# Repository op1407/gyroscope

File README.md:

# gyroscope

A simple Gyroscope using RP2040 based PCB, MPU-6050 and ST7735 1,8" TFT Display

3D model was created using DesignSpark Mechanical 5.0

PCB was created using KiCad 6.0

License: CC BY 4.0
https://creativecommons.org/licenses/by/4.0/

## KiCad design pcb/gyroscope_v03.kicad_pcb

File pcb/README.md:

# KiCad files

PCB design files

Some symbols and footprints are also missing

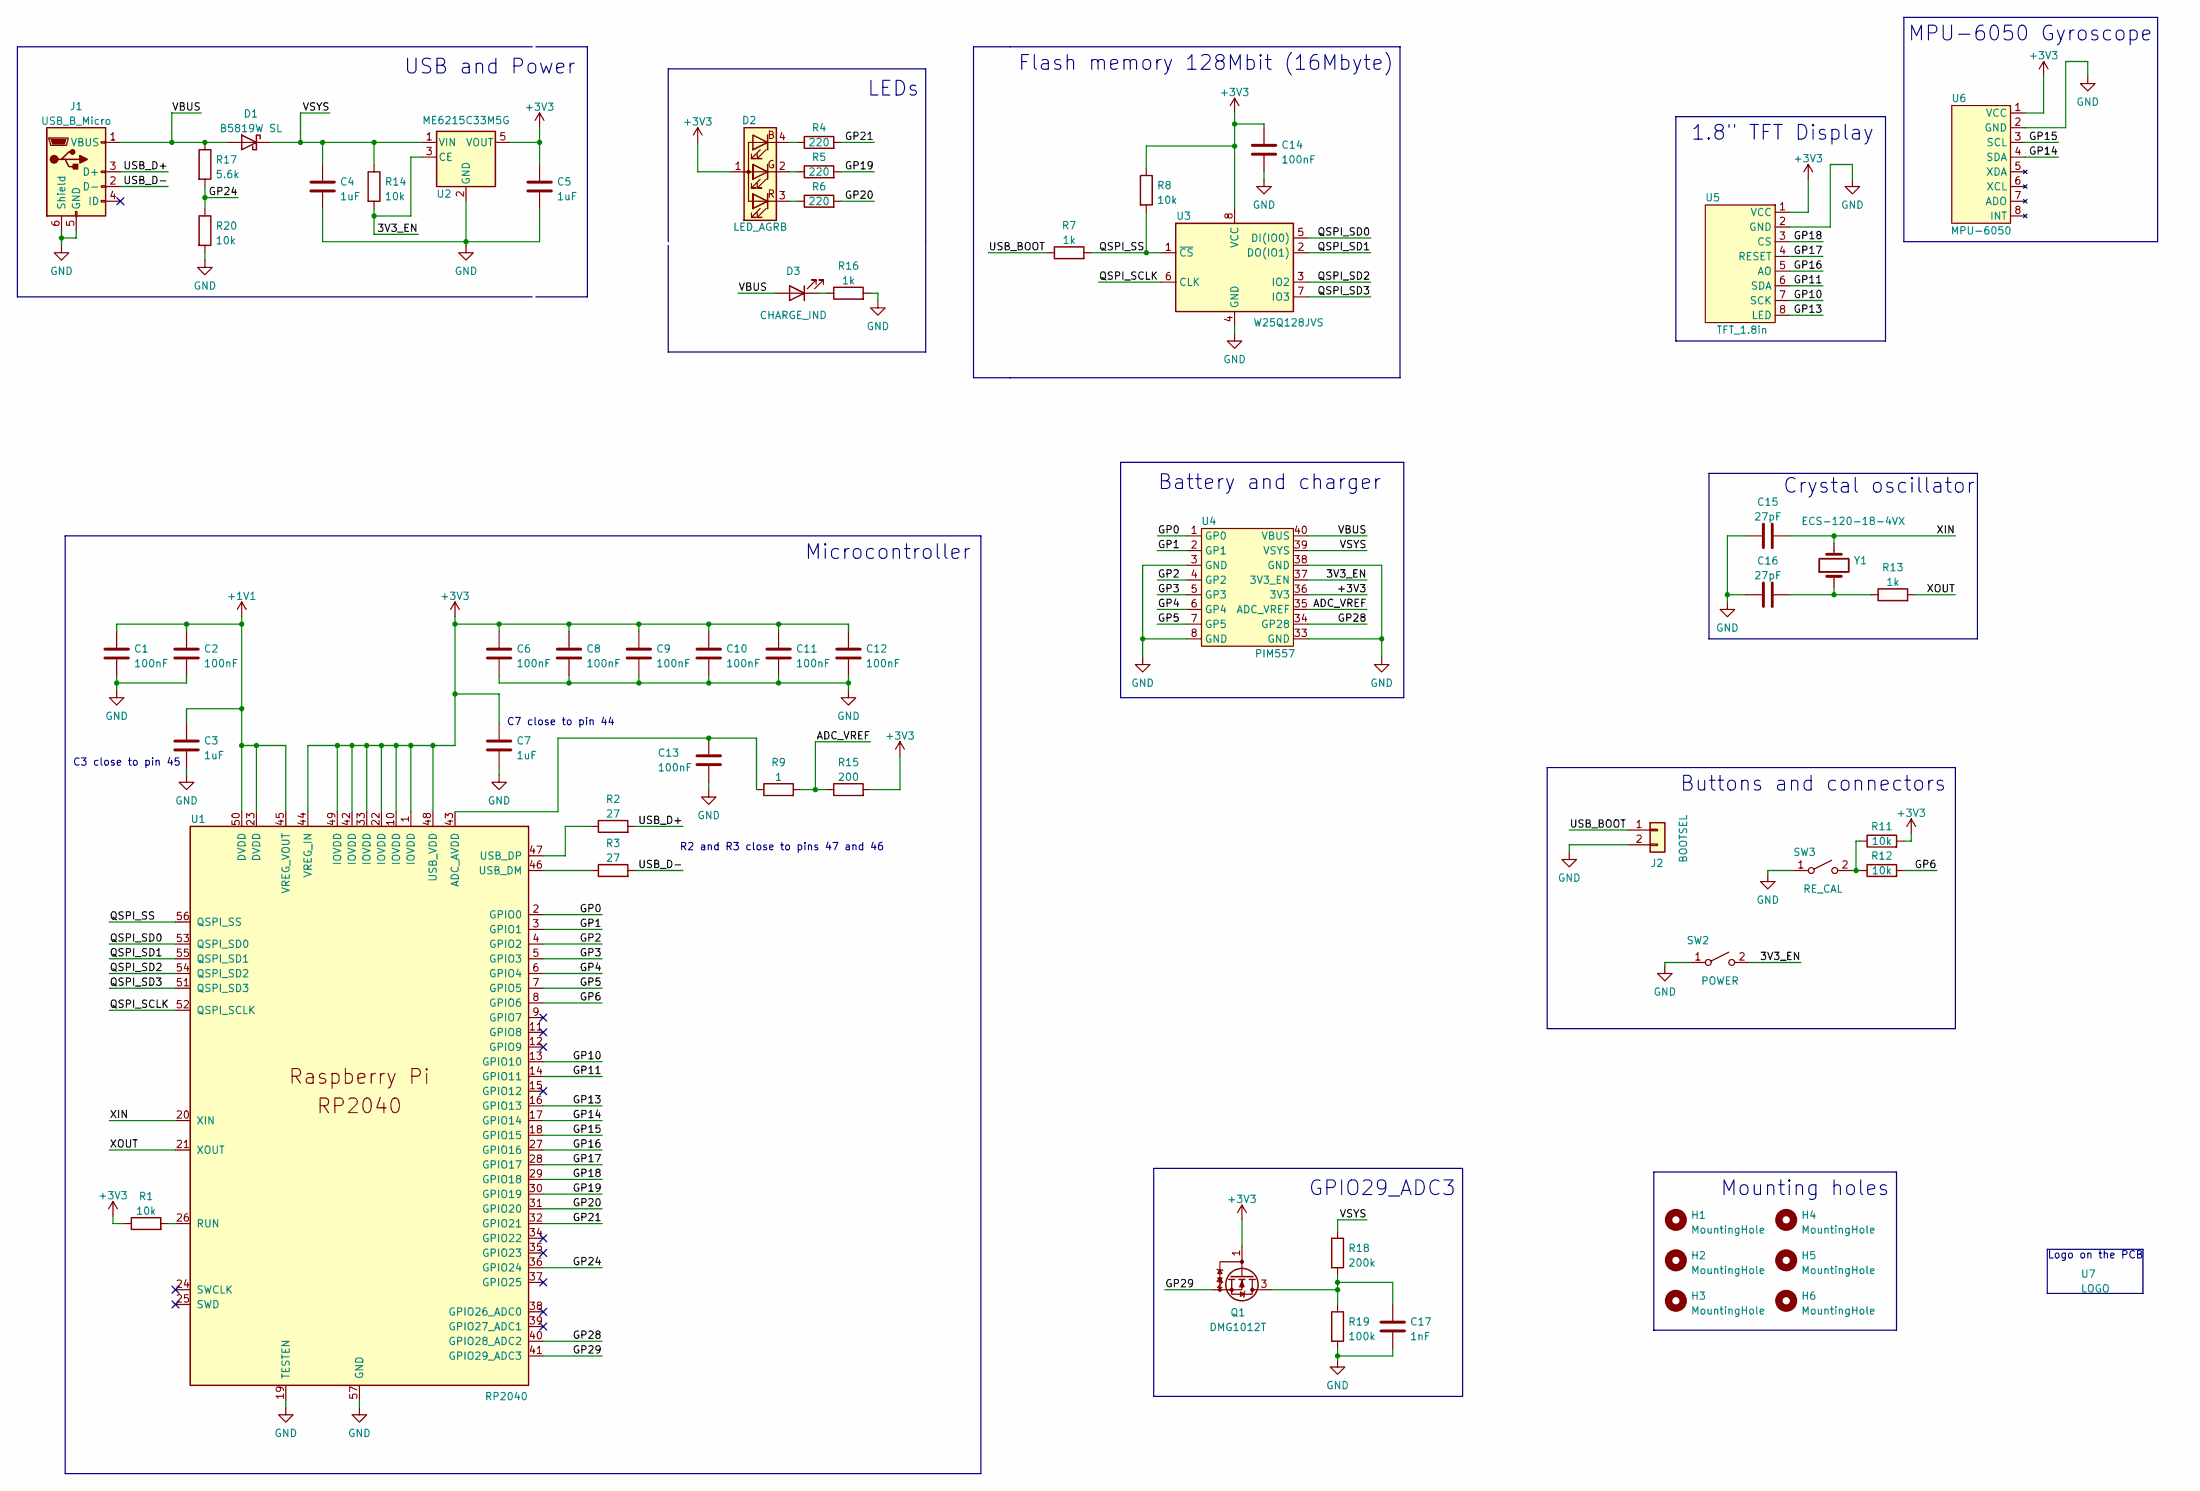
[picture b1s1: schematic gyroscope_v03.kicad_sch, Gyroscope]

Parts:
C1, C2, C6, C8, C9, C10, C11, C12, C13, C14: 100nF; C_0402_1005Metric
C3, C4, C5, C7: 1uF; C_0402_1005Metric
C15, C16: 27pF; C_0402_1005Metric
C17: 1nF; C_0402_1005Metric
D1: B5819W SL; D_SOD-123; LCSC C8598
D2: LED_AGRB; RGB_LED
D3: CHARGE_IND; CHR_LED
H1, H2, H3, H4, H6: MountingHole; MountingHole_3.2mm_M3
H5: MountingHole; MountingHole_2.7mm_M2.5
J1: USB_B_Micro; USB 2.0 Micro B; LCSC C132563
J2: BOOTSEL; PinHeader_1x02_P2.54mm_Horizontal
Q1: DMG1012T; SOT-523; LCSC C2830301
R1, R8, R11, R12, R14, R20: 10k; R_0402_1005Metric
R2, R3: 27; R_0402_1005Metric
R4, R5, R6: 220; R_0402_1005Metric
R7, R13, R16: 1k; R_0402_1005Metric
R9: 1; R_0402_1005Metric
R15: 200; R_0402_1005Metric
R17: 5.6k; R_0402_1005Metric
R18: 200k; R_0402_1005Metric
R19: 100k; R_0402_1005Metric
SW2: POWER; PinHeader_1x02_P2.54mm_Horizontal
SW3: RE_CAL; PinHeader_1x02_P2.54mm_Horizontal
U1: RP2040; RP2040-QFN-56
U2: ME6215C33M5G; SOT-23-5
U3: W25Q128JVS; SOIC-8_5.23x5.23mm_P1.27mm
U4: PIM557
U5: TFT_1.8in
U6: MPU-6050; MPU-6050_pcb
U7: LOGO; logo_mirrored
Y1: ECS-120-18-4VX; Crystal_HC49-U_Vertical

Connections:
+1V1: C1.1, C2.1, C3.1, U1.23 (DVDD), U1.45 (VREG_VOUT), U1.50 (DVDD)
+3V3: C5.1, C6.1, C7.1, C8.1, C9.1, C10.1, C11.1, C12.1, C14.1, D2.1 (A), Q1.1 (G), R1.1, R8.1, R11.2, R15.2, U1.1 (IOVDD), U1.10 (IOVDD), U1.22 (IOVDD), U1.33 (IOVDD), U1.42 (IOVDD), U1.44 (VREG_IN), U1.48 (USB_VDD), U1.49 (IOVDD), U2.5 (VOUT), U3.8 (VCC), U4.36 (3V3), U5.1 (VCC), U6.1 (VCC)
/3V3_EN: R14.2, SW2.2 (B), U2.3 (CE), U4.37 (3V3_EN)
/ADC_VREF: R9.2, R15.1, U4.35 (ADC_VREF)
/GP0: U1.2 (GPIO0), U4.1 (GP0)
/GP1: U1.3 (GPIO1), U4.2 (GP1)
/GP2: U1.4 (GPIO2), U4.4 (GP2)
/GP3: U1.5 (GPIO3), U4.5 (GP3)
/GP4: U1.6 (GPIO4), U4.6 (GP4)
/GP5: U1.7 (GPIO5), U4.7 (GP5)
/GP6: R12.2, U1.8 (GPIO6)
/GP10: U1.13 (GPIO10), U5.7 (SCK)
/GP11: U1.14 (GPIO11), U5.6 (SDA)
/GP13: U1.16 (GPIO13), U5.8 (LED)
/GP14: U1.17 (GPIO14), U6.4 (SDA)
/GP15: U1.18 (GPIO15), U6.3 (SCL)
/GP16: U1.27 (GPIO16), U5.5 (AO)
/GP17: U1.28 (GPIO17), U5.4 (RESET)
/GP18: U1.29 (GPIO18), U5.3 (CS)
/GP19: R5.2, U1.30 (GPIO19)
/GP20: R6.2, U1.31 (GPIO20)
/GP21: R4.2, U1.32 (GPIO21)
/GP24: R17.2, R20.1, U1.36 (GPIO24)
/GP28: U1.40 (GPIO28_ADC2), U4.34 (GP28)
/GP29: Q1.2 (S), U1.41 (GPIO29_ADC3)
/QSPI_SCLK: U1.52 (QSPI_SCLK), U3.6 (CLK)
/QSPI_SD0: U1.53 (QSPI_SD0), U3.5 (DI(IO0))
/QSPI_SD1: U1.55 (QSPI_SD1), U3.2 (DO(IO1))
/QSPI_SD2: U1.54 (QSPI_SD2), U3.3 (IO2)
/QSPI_SD3: U1.51 (QSPI_SD3), U3.7 (IO3)
/QSPI_SS: R7.2, R8.2, U1.56 (QSPI_SS), U3.1 (~CS)
/USB_BOOT: J2.1, R7.1
/USB_D+: J1.3 (D+), R2.2
/USB_D-: J1.2 (D-), R3.2
/VBUS: D1.2 (A), D3.2 (A), J1.1 (VBUS), R17.1, U4.40 (VBUS)
/VSYS: C4.1, D1.1 (K), R14.1, R18.1, U2.1 (VIN), U4.39 (VSYS)
/XIN: C15.2, U1.20 (XIN), Y1.2
/XOUT: R13.2, U1.21 (XOUT)
GND: C1.2, C2.2, C3.2, C4.2, C5.2, C6.2, C7.2, C8.2, C9.2, C10.2, C11.2, C12.2, C13.2, C14.2, C15.1, C16.1, C17.2, J1.5 (GND), J1.6 (Shield), J2.2, R16.2, R19.2, R20.2, SW2.1 (A), SW3.1 (A), U1.19 (TESTEN), U1.57 (GND), U2.2 (GND), U3.4 (GND), U4.3 (GND), U4.8 (GND), U4.33 (GND), U4.38 (GND), U5.2 (GND), U6.2 (GND)
unnamed: C13.1, R9.1, U1.43 (ADC_AVDD)
unnamed: C16.2, R13.1, Y1.1
unnamed: C17.1, Q1.3 (D), R18.2, R19.1
unnamed: D2.2 (GK), R5.1
unnamed: D2.3 (RK), R6.1
unnamed: D2.4 (BK), R4.1
unnamed: D3.1 (K), R16.1
unnamed: R1.2, U1.26 (RUN)
unnamed: R2.1, U1.47 (USB_DP)
unnamed: R3.1, U1.46 (USB_DM)
unnamed: R11.1, R12.1, SW3.2 (B)

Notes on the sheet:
Logo on the PCB
MPU-6050 Gyroscope
Battery and charger
Buttons and connectors
Flash memory 128Mbit (16Mbyte)
Crystal oscillator
LEDs
Mounting holes
R2 and R3 close to pins 47 and 46
USB and Power
C7 close to pin 44
GPIO29_ADC3
1.8" TFT Display
Microcontroller
C3 close to pin 45

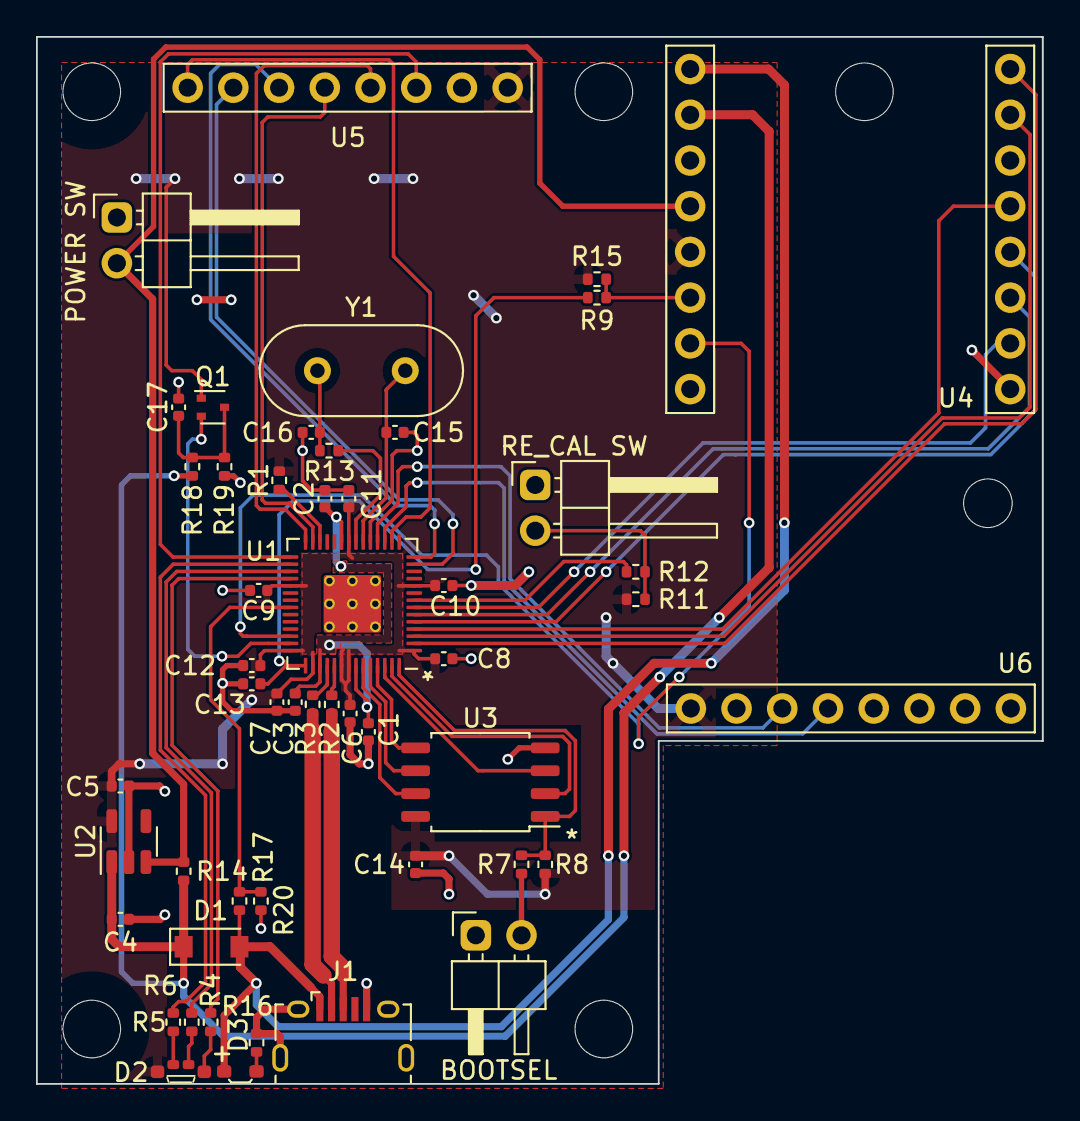
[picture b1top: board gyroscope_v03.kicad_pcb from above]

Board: 2 copper layers, 55.9 x 58.2 mm, 58 parts (0 on the bottom side), 50 nets.

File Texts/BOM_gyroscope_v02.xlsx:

Comment | Designator | Footprint | JLCPBC Part # | Quantity
27 | R3,R2 | 0402 | C25100 | 2
220 | R5,R4,R6 | 0402 | C25091 | 3
100nF | C13,C9,C1,C2,C10,C6,C14,C11,C12,C8 | 0402 | C1525 | 10
10k | R1,R14,R8,R10,R11,R12,R9 | 0402 | C25744 | 7
10uF | C17 | 0402 | C15525 | 1
1k | R7,R13 | 0402 | C11702 | 2
1uF | C5,C3,C7,C4 | 0402 | C52923 | 4
27pF | C15,C16 | 0402 | C1557 | 2
B5819W SL | D1 | SOD-123 | C8598 | 1
LED_AGRB | D2 | SMD | C181865 | 1
ME6215C33M5G | U2 | SOT-23-5 | C84119 | 1
RP2040 | U1 | LQFN-56_EP_7.0x7.0x0.4P | C2040 | 1
USB_B_Micro | J1 | MICRO-USB-SMD | C132563 | 1
W25Q128JVS | U3 | SOIC-8_5.3x5.3x1.27P | C97521 | 1

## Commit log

2022-03-24 Rename .gitkeep to README.md
2024-11-04 Added images of schematics
2024-11-04 Added BOM and CPL

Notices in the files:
pcb/gyroscope_v03.kicad_sch:
https://creativecommons/licenses/by/4.0
